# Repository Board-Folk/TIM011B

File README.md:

# TIM-011B

An updated remake of the TIM-011 computer from Serbia.

This repository contains the Bill-of-Materials (BOM), Gerbers and Kicad files for a remake of the TIM-011 from the Mihajlo Pupin Institute of Serbia, 1987.

The TIM-011 is a CP/M based computer that uses the Z80 family Hitachi HD64180 processor with 256KB RAM, 4 scale monochrome video and a FDC9266 floppy disk controller on the main board. It has an expansion bus, serial and parallel port and an ASCII keyboard interface. The system is built entirely from off-the-shelf parts that were commonly available at the time without any custom ULA or gate array chips. Most parts remain relatively easy to get hold of today online.

Version 1.1 does not deviate from the original board too much so it can still be considered a replica.

Version 1.2 includes 5V only operation, but due to stability issues this has not been published.

Version 1.3 contains improvements including composite video output, updated oscillators and stability fixes and uses a GAL for video sync signals. The initial version of this GAL is incompatible with the original screen, a modified version may be added in the future. From version 1.3, the board changed from using HC-49 crystals to TTL output DIP8 layout "square" can type oscillators.

Feel free to fork and make your own mods outside of this repository. Folder Extensions contains add on expansions and adapters for the board. More will follow over time.

The work-in-progress version of the board has been removed from this project. If you're looking to make one, pick the latest version from the Releases folder.

Projects are in Kicad 8.

## Building the board

A BOM is present in each release folder. The Kicad iBOM plugin has also been used to create an interactive BOM in the BOM subfolders for the main boards and expansion boards. Since these builds use obsolete parts, such as the CPU, FDC and RAM, we cannot provide any links to those parts. They are available on AliExpress and eBay, but many sellers will ship relabeled or faulty ICs. Be careful.

## Using the board

### Power

Version 1.1, as the original board requires 5V, 12V and -12V power. Power connectors on the board are the original Ei Niš connector P2, but due to the lack of availability of this part we've added P5, a standard 4 pin 3.96mm pin header to the rear of the board. 

Version 1.3 has a centre positive DC barrel jack for only 5V operation also.

### Video

Original video output is not standard, conversion is needed for use on a modern display. This works directly with the original screen and is the only output option on boards until version v1.3. The video fix extension board gives conversion to composite video for boards up to release v1.1. As a technical note, the original video output is provided as 2 TTL signals to giving 4 shades, with a relatively wide horizonal and vertical sync for the original CRT. The horizontal sync is in an awkward position and is more simlar to horizonal drive found on comparible systems with a simple in-build CRT display.

Version 1.3 adds a composite video output for use on standard monitors.

### Keyboard

The keyboard is serial ASCII, 9600 8E1 with a 12V power output on the 5 pin DIN header. Version 1.3 adds the option to switch this to 5V operation. Adapter boards are being added to the extensions folder for this and will also including modules for the v1.3 mainboard to contain keyboard conversion within the board footprint.

No operating system is included within the ROM - it needs to boot this from floppy disk or equivalent Gotek or Flash Floppy device. Marko's updated ROM for v1.3, which is backwards compatable adds diagnotics and support to boot from CF cards with the 8 bit CF/IDE expansion board and adapter.

More information to follow.

## TIM011 Resources

Marko Šolajić has put a great page together with a ROM, boot disks, software and other resources to help get the TIM-011 going. Highly recommended. The standard "sys", system ROM is 8KB, this will fit on the currently still manufactured and widely available AT28C64B.

  [TIM011 Resources](https://blog.8bitchip.info/tim011-resources/)
  
Marko is also documenting system software and has provided a new boot ROM. These can be found here:

  [TIM011 System Software](https://github.com/msolajic/tim011-system-software)

## Revisions

* Version 1.1 Initial Public Release
* Version 1.2 Unreleased
* Version 1.3 Current Release
  
### Version 1 Modifications from Original

* Fixed VSYNC Buffer
* Fix Strobe Pullup
* CX timing fix capacitor
* P5 3.96mm right angle power pin header 
* XT Keyboard INT0/SCROLL fix modification with JMP3 selection on/off
* Right angle reset momentatary switch within T1 footprint
* Modernise J3 keyboard connector footprint
* J4 and J5 serial pin headers for alternative serial connections
* Added mounting holes
* Power LED

### Version 1.1

* C42 silkscreen
* Fix J4 and J5 connections
* Silkscreen updates
* ROM A13 to GND
* Increase DB25 mounting point radius to 1.6mm
* Add JMP4 drive Ready/Disk Change modification

### Version 1.2

* 5V Only operation - added DC barrel jack
* Ceramic caps changed to 5.08mm
* Updated silkscreen
* JMP5 5V/12V keyboard selection
* A13,A14,A15 ROM options
* JMP8 No Video jumper
* Change serial to MAX232 (5V)
* RAM change to 44256
* "Half-can" Oscillators for X1 and X2
* JMP9 12V Power selection for expansion bus pin 40
* Grounding point
* Support for keyboard modules

### Version 1.3

* Replaced U2 74LS08 with GAL16V8
* Sync signals negative with standard GAL
* Change serial port to 9 pin
* Oscillators now buffered
* R8 reset pullup
* Composite video output

## Version 1.3 BOM

There are 3 options for board power, P2, P5 or P7. Ceramic capacitors 5.08mm and resistors 1/4W.

|Qty|Reference(s)|Value|Type|Notes|
|:--:|:--:|:--:|:--:|:--:|
|1|P1|5-7 pin header|Header|Video|
|1|P3|2x20 pin header|Dual Row 2.54mm Header|Expansion|
|1|P4|2x17 pin header|Dual Row 2.54mm Header|Floppy|
|1|P2|Unknown Ei Niš 4 pin header|Header|Power|
|1|P5|3.96mm 4 pin header|3.96mm Header|Alt Power|
|1|P7|DC Barrel Jack||5V Power|
|1|P8|RCA Jack||Composite Output|
|46|C3, C8, C10-C53|100nF|Ceramic Capacitor||
|1|C2|1nF|Ceramic Capacitor||
|1|C4|10uF 16V|Axial or Radial||
|1|C5|2n2|Ceramic Capacitor||
|1|C6|470uF 25V|Axial or Radial||
|8|C54-C57, C58-C61|1uF 16V|Radial||
|1|CX1, CX2|330pF|Ceramic Capacitor||
|1|D1|1N4148|Diode||
|1|D1|3mm LED|LED||
|2|R1, R12|470R|Resistor||
|1|R10|1K5|Resistor||
|1|R11|5K1|Resistor||
|2|R13, R20|1K|Resistor||
|1|R14|220R|Resistor||
|1|R15|10K|Resistor||
|1|R16|68R|Resistor||
|5|R2-R5, R7|4K7|Resistor||
|1|R6|100R|Resistor||
|1|R8|56K|Resistor||
|1|R9|2K2|Resistor||
|2|RP1, RP2|4K7 SIP10 Bussed|Resistor Network||
|1|RP3|330R SIP10 Bussed|Resistor Network||
|1|Q1|BC557|Transistor||
|1|U17|HD64180|IC|CPU|
|1|U43|FDC9266|IC|Floppy Controller|
|2|U8, U9|MAX232|IC|Serial Line Driver/Receiver|
|1|U16|27xxx ROM|IC|System ROM|
|2|U60, U61|44256 DRAM|IC|System RAM|
|1|U30|43256 SRAM|IC|Video RAM|
|1|U2|GAL16V8|IC|Sync Logic|
|1|U1|74LS08|IC||
|2|U11, U12|74LS283|IC||
|2|U14, U44|74LS240|IC||
|1|U18|74LS20|IC||
|7|U19-U22, U26-U28|74LS157|IC||
|1|U23|74LS00|IC||
|1|U24|74LS04|IC||
|1|U29|74HC153|IC||
|2|U3, U13|74HC4040|IC||
|1|U31|74LS32|IC||
|1|U32|74LS139|IC||
|1|U33|74LS07|IC||
|1|U34|74LS06|IC||
|1|U35|74LS158|IC||
|5|U4-U6, U40, U41|74LS374|IC||
|1|U42|74LS244|IC||
|4|U7, U10, U15, U25|74LS74|IC||
|1|T1|Unknown Reset Switch|Switch|T1 or T2|
|1|T2|RA Momentary Switch|Switch||
|1|J1|DB25 Female Right Angle|Socket|Printer|
|1|J3|5 pin DIN|Socket|180 degree / ASCII Keyboard|
|2|J4, J5|4 pin header|2.54mm Header|Alt TTL Serial|
|1|J6|DB9 Male Right Angle|Socket|Serial|
|1|JMP1, JMP3, JMP5-8|3 pin header|2.54mm Header||
|1|JMP2|5 pin header|2.54mm Header||
|1|JMP4|2 pin header|2.54mm Header|Fix Ready/Disk Change|
|1|X1|12.288MHz TTL Osc Can (DIP8)|Oscillator||
|1|X2|8MHz TTL Osc Can (DIP8)|Oscillator||

## Jumper Settings

Version 1.3

|Jumper|Description|Default|
|:--:|:--:|:--:|
|JMP1|CTS0 Select|2-3|
|JMP2|CTS/DCD Select|4-5,7-8|
|JMP3|XT Keyboard Fix|1-2 D Normal, 2-3 U Fix|
|JMP4|FDC Ready|Optional|
|JMP5|Keyboard Power|1-2 D 12V, 2-3 U 5V|
|JMP6|ROM A14|1-2 L 5V, 2-3 R A14|
|JMP7|ROM A15|1-2 L 5V, 2-3 R A15|
|JMP8|Video Bypass|1-2 U Normal, 2-3 D Disable|
|JMP9|12V Expansion Pin 40|NF|
|JMP10|HSYNC connection for CSYNC|Preset ON|

## Links

   [Marko's Blog Post on the TIM 011](https://blog.8bitchip.info/482-tim-011-a-new-life-for-an-old-computer/)

## Credits

PCB Layout by Rob Taylor @peepouk, Ian Cudlip @grandoldian and Marko Šolajić @msolajic. Schematics recreated and modifications by Ian Cudlip and Marko Šolajić. Special thanks to @demerzel, your schematics have helped and saved time.

## Thanks

* Zoltan Pekic
* @demerzel
* The Board Folk Team

## Legal

As the product of this project is a replica of a proprietary product, the the author makes no claim of copyright to the schematics nor PCB layouts and releases these into the public domain, solely for the purposes of study and historical preservation.

You are free to produce PCBs based on this project's designs at your own risk and without limitation, for your own use or for sale and/or repair at a reasonable price. Attribution is appreciated. The authors are not obliged to provide support of any kind. 

Under no circumstances will the authors be held responsible or liable in any way for losses, damages or costs resulting from the use of the information and/or resources of this project. 

The resources are provided "as-is" without warranty of any kind, either expressed or implied, including, but not limited to, the implied warranties of merchantability and fitness for a particular purpose.

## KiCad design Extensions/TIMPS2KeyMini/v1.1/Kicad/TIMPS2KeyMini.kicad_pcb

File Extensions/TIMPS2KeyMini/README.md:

# TIMPS2KeyMini

ATMega328 based PS/2 Keyboard Adapter. A daugherboard that will fit within the mainboard footprint instead of the traditional 5 pin DIN ASCII keyboard socket. This includes the i2c connector for the TIMI2CLEDPanel board which provides the LEDs.

## Versions

v1.1 Initial release

## Main board modifications

This fits instead of the external RS232 functionality of the original keyboard and connector (serial port RS232 remains). On the mainboard, do not fit the MAX232 at J9, the 5 pin DIN socket J3 and the charge caps C58-C61, fitting the 4 pin header J5 instead. Standoffs will needed to be mounted to secure the mini keyboard board and the pin length of the J5 header should match the standoff length. Recommendations may follow.

## Programming the ATMega328

The board doesn't include a programming header, the ATMega328 chip needs programming separately. The simplest way of doing this is with a Minipro with the appopriate fuse settings set in Xgpro. Tested settings are in the screenshot below and the exported binary and hex files for programming can be found in the export folder. For the arduino code see the main TIMPS2Key extension folder.

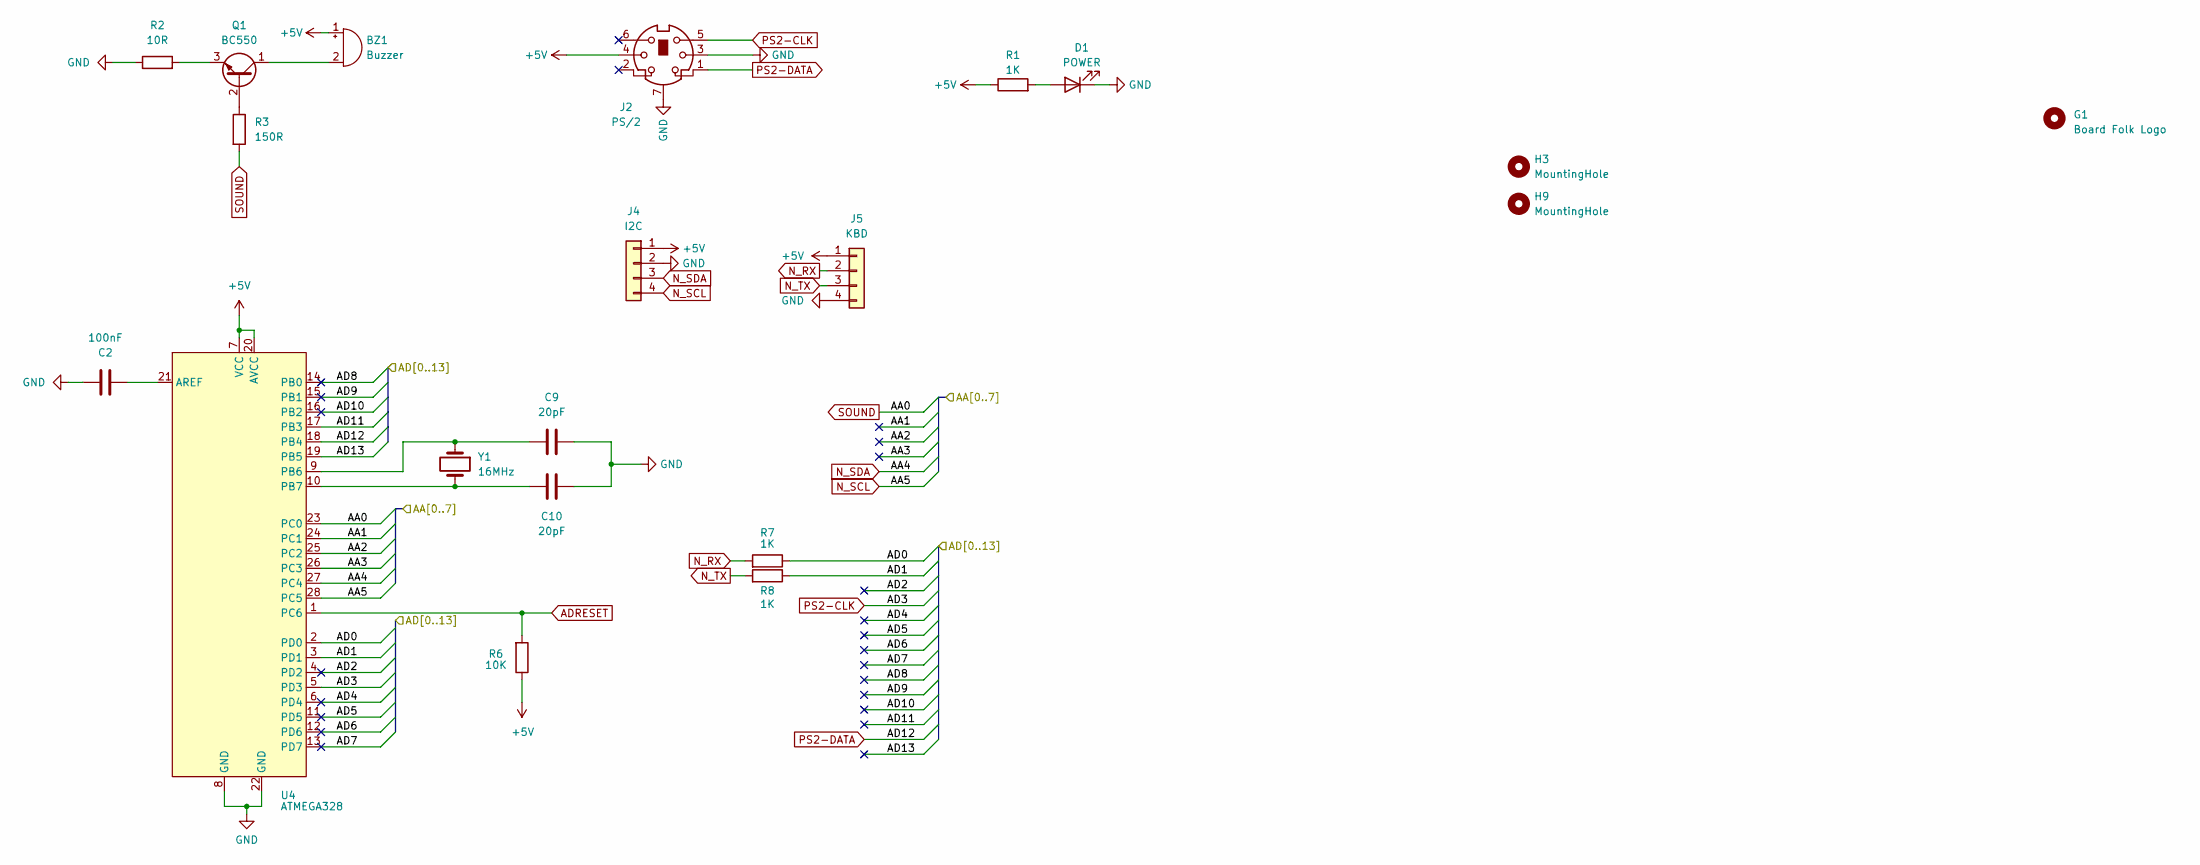
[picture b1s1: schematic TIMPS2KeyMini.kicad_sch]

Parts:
BZ1: Buzzer
C2: 100nF; Ceramic Cap 5.08mm
C9, C10: 20pF; Ceramic Cap 5.08mm
D1: POWER; LED_D3.0mm
G1: Board Folk Logo; BF8
H3, H9: MountingHole; MountingHole_M2.5
J2: PS/2; Connector_Mini-DIN_Female_6Pin_2rows
J4: I2C; PinHeader_1x04_2.54mm
J5: KBD; PinHeader_1x04_2.54mm
Q1: BC550; TO-92_Inline_Wide
R1, R7, R8: 1K; Resistor 7.62mm
R2: 10R; Resistor 7.62mm
R3: 150R; Resistor 7.62mm
R6: 10K; Resistor 7.62mm
U4: ATMEGA328; DIP-28_W7.62mm_Socket
Y1: 16MHz; Crystal_HC49-U_Vertical

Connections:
+5V: BZ1.1 (+), J2.4, J4.1, J5.1, R1.1, R6.1, U4.7 (VCC), U4.20 (AVCC)
/AA1: U4.24 (PC1)
/AA2: U4.25 (PC2)
/AA3: U4.26 (PC3)
/AD0: R7.1, U4.2 (PD0)
/AD1: R8.1, U4.3 (PD1)
/AD2: U4.4 (PD2)
/AD4: U4.6 (PD4)
/AD5: U4.11 (PD5)
/AD6: U4.12 (PD6)
/AD7: U4.13 (PD7)
/AD8: U4.14 (PB0)
/AD9: U4.15 (PB1)
/AD10: U4.16 (PB2)
/AD11: U4.17 (PB3)
/AD13: U4.19 (PB5)
ADRESET: R6.2, U4.1 (PC6)
GND: C2.2, C9.2, C10.2, D1.1 (K), J2.3, J2.7, J4.2, J5.4, R2.1, U4.8 (GND), U4.22 (GND)
N_RX: J5.2, R7.2
N_SCL: J4.4, U4.28 (PC5)
N_SDA: J4.3, U4.27 (PC4)
N_TX: J5.3, R8.2
unnamed: BZ1.2 (-), Q1.1 (C)
unnamed: D1.2 (A), R1.2
unnamed: Q1.2 (B), R3.1
unnamed: Q1.3 (E), R2.2
unnamed: C2.1, U4.21 (AREF)
unnamed: C9.1, U4.9 (PB6), Y1.1
unnamed: C10.1, U4.10 (PB7), Y1.2
PS2-CLK: J2.5, U4.5 (PD3)
PS2-DATA: J2.1, U4.18 (PB4)
SOUND: R3.2, U4.23 (PC0)

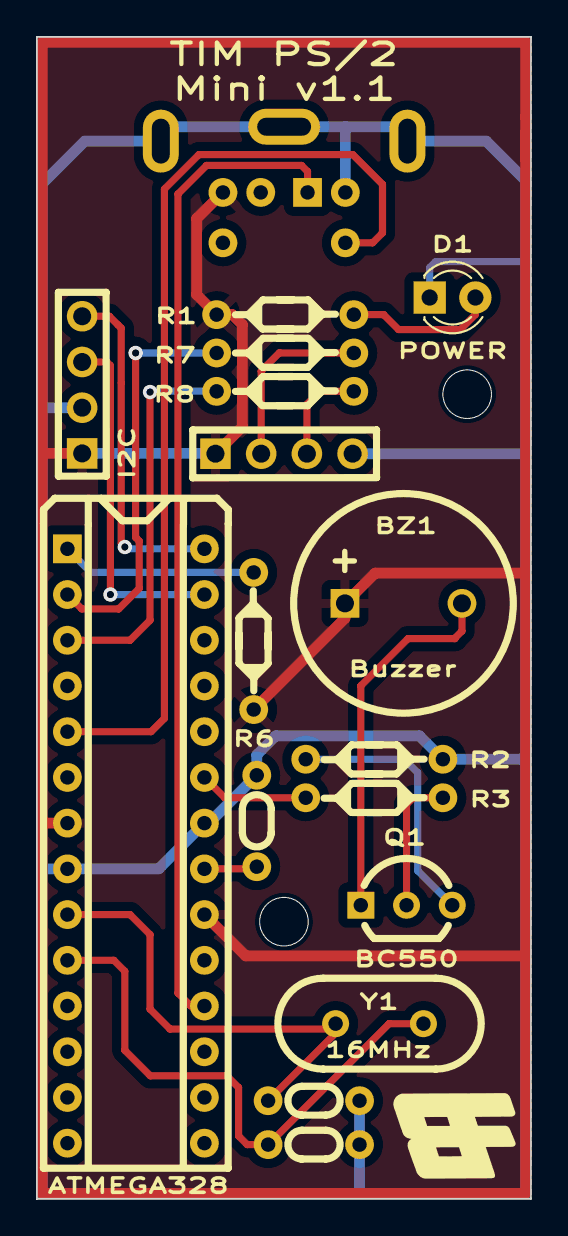
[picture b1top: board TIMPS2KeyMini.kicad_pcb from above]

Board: 2 copper layers, 27.5 x 64.6 mm, 20 parts (1 on the bottom side), 19 nets.

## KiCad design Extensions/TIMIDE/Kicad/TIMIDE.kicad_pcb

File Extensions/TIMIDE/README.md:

# TIMIDE

An 8-bit IDE and Compact Flash interface for the TIM-011 for the expansion header. This requires the updated ROM by Marko Šolajić which can be found here:

  [TIM011 System Software](https://github.com/msolajic/tim011-system-software)

The default IO address for the board as used by the ROM, selectable by jumper is E8. To date we've not found an 8 bit compatable IDE hard disk to work with this board, but a standard Amazon / AliExpress CompactFlash to IDE adapter works fine (pictured).

Marko's site also provides a CF image to get things going.

## Versions

v1 Initial release

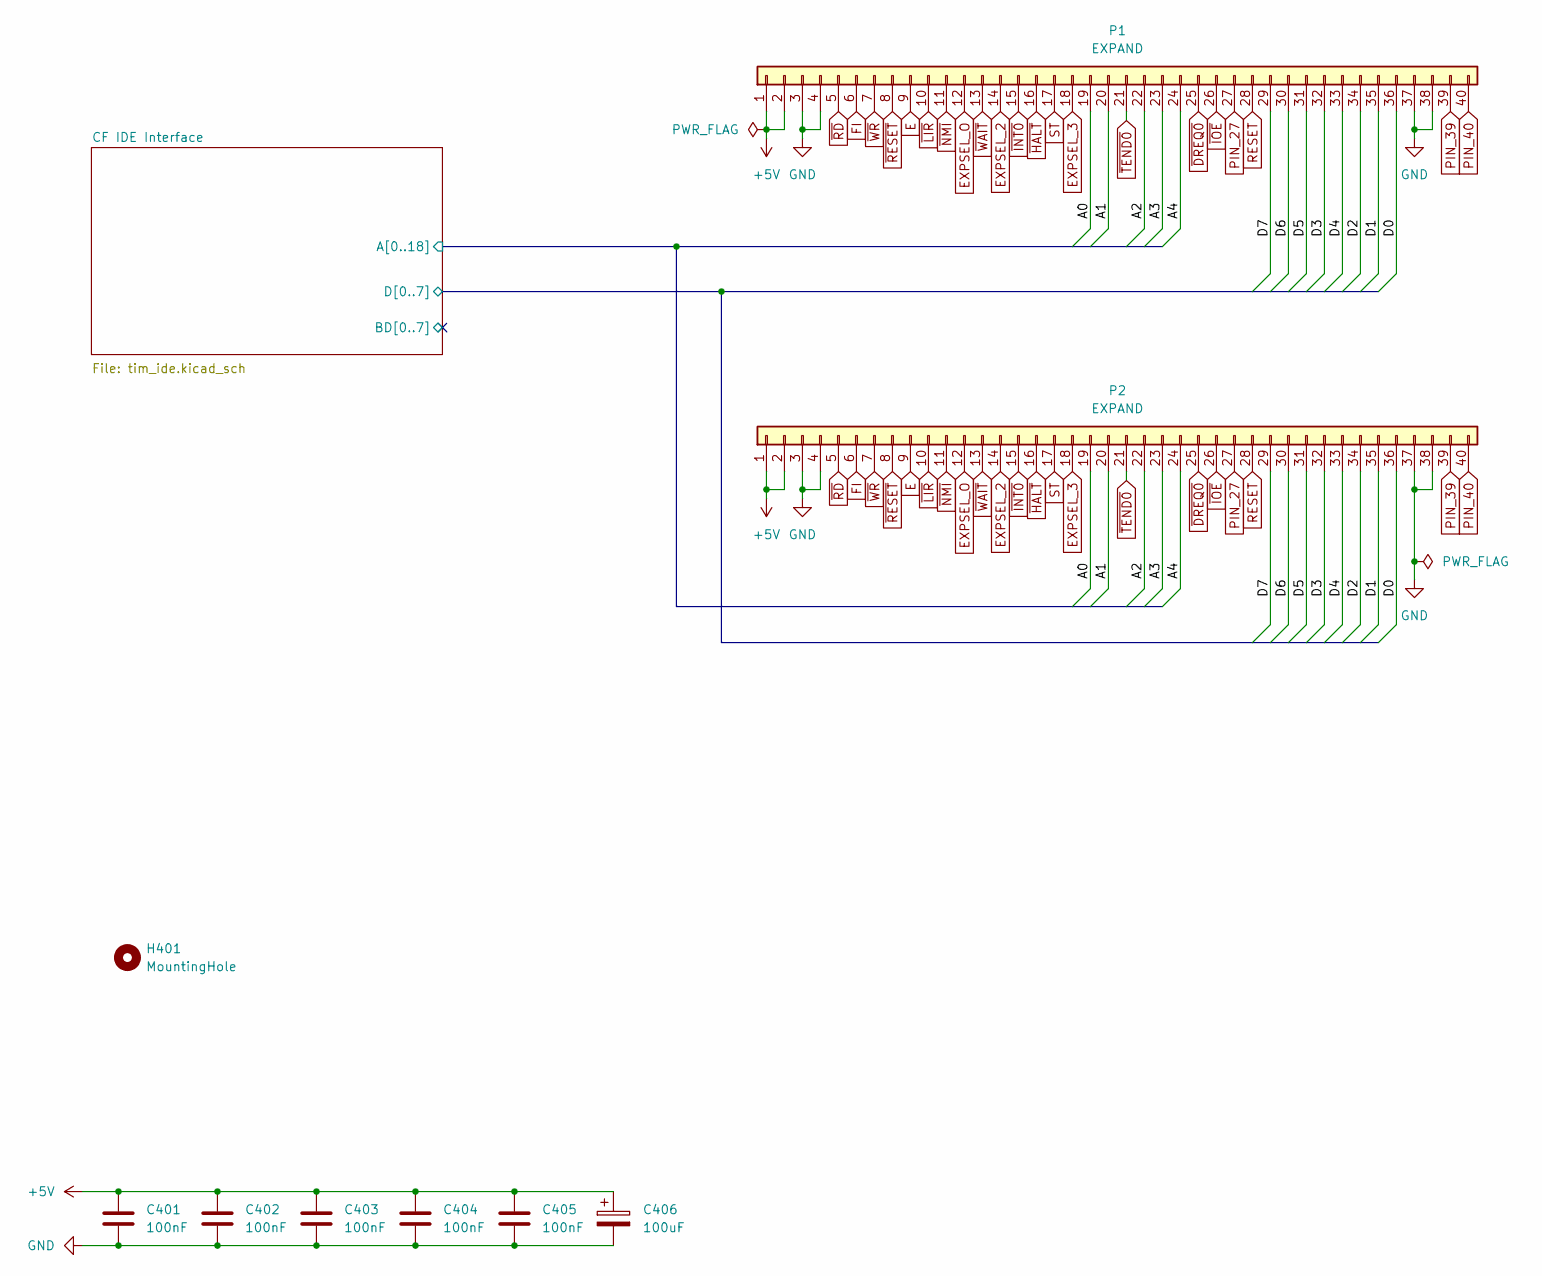
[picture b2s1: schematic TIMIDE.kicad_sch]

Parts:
C401, C402, C403, C404, C405: 100nF; Ceramic Cap 5.00mm
C406: 100uF; Electrolytic Capacitor Axial or Radial Alt
H401: MountingHole; MountingHole_M2.5
P1, P2: EXPAND; PinHeader_2x20 2.54mm

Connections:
+5V: C401.1, C402.1, C403.1, C404.1, C405.1, C406.1, P1.1, P1.2, P2.1, P2.2; also elsewhere on the board
/CF IDE Interface/A0: P1.19, P2.19; also elsewhere on the board
/CF IDE Interface/A1: P1.20, P2.20; also elsewhere on the board
/CF IDE Interface/A2: P1.22, P2.22; also elsewhere on the board
/CF IDE Interface/A3: P1.23, P2.23; also elsewhere on the board
/CF IDE Interface/A4: P1.24, P2.24; also elsewhere on the board
/CF IDE Interface/D0: P1.36, P2.36; also elsewhere on the board
/CF IDE Interface/D1: P1.35, P2.35; also elsewhere on the board
/CF IDE Interface/D2: P1.34, P2.34; also elsewhere on the board
/CF IDE Interface/D3: P1.32, P2.32; also elsewhere on the board
/CF IDE Interface/D4: P1.33, P2.33; also elsewhere on the board
/CF IDE Interface/D5: P1.31, P2.31; also elsewhere on the board
/CF IDE Interface/D6: P1.30, P2.30; also elsewhere on the board
/CF IDE Interface/D7: P1.29, P2.29; also elsewhere on the board
E: P1.9, P2.9
EXPSEL_2: P1.14, P2.14
EXPSEL_3: P1.18, P2.18
EXPSEL_O: P1.12, P2.12; also elsewhere on the board
FI: P1.6, P2.6; also elsewhere on the board
GND: C401.2, C402.2, C403.2, C404.2, C405.2, C406.2, P1.3, P1.4, P1.37, P1.38, P2.3, P2.4, P2.37, P2.38; also elsewhere on the board
PIN_27: P1.27, P2.27
PIN_39: P1.39, P2.39
PIN_40: P1.40, P2.40
RESET: P1.28, P2.28
ST: P1.17, P2.17
~DREQ0: P1.25, P2.25
~HALT: P1.16, P2.16
~INT0: P1.15, P2.15
~IOE: P1.26, P2.26
~LIR: P1.10, P2.10; also elsewhere on the board
~NMI: P1.11, P2.11
~RD: P1.5, P2.5; also elsewhere on the board
~RESET: P1.8, P2.8; also elsewhere on the board
~TEND0: P1.21, P2.21
~WAIT: P1.13, P2.13
~WR: P1.7, P2.7; also elsewhere on the board

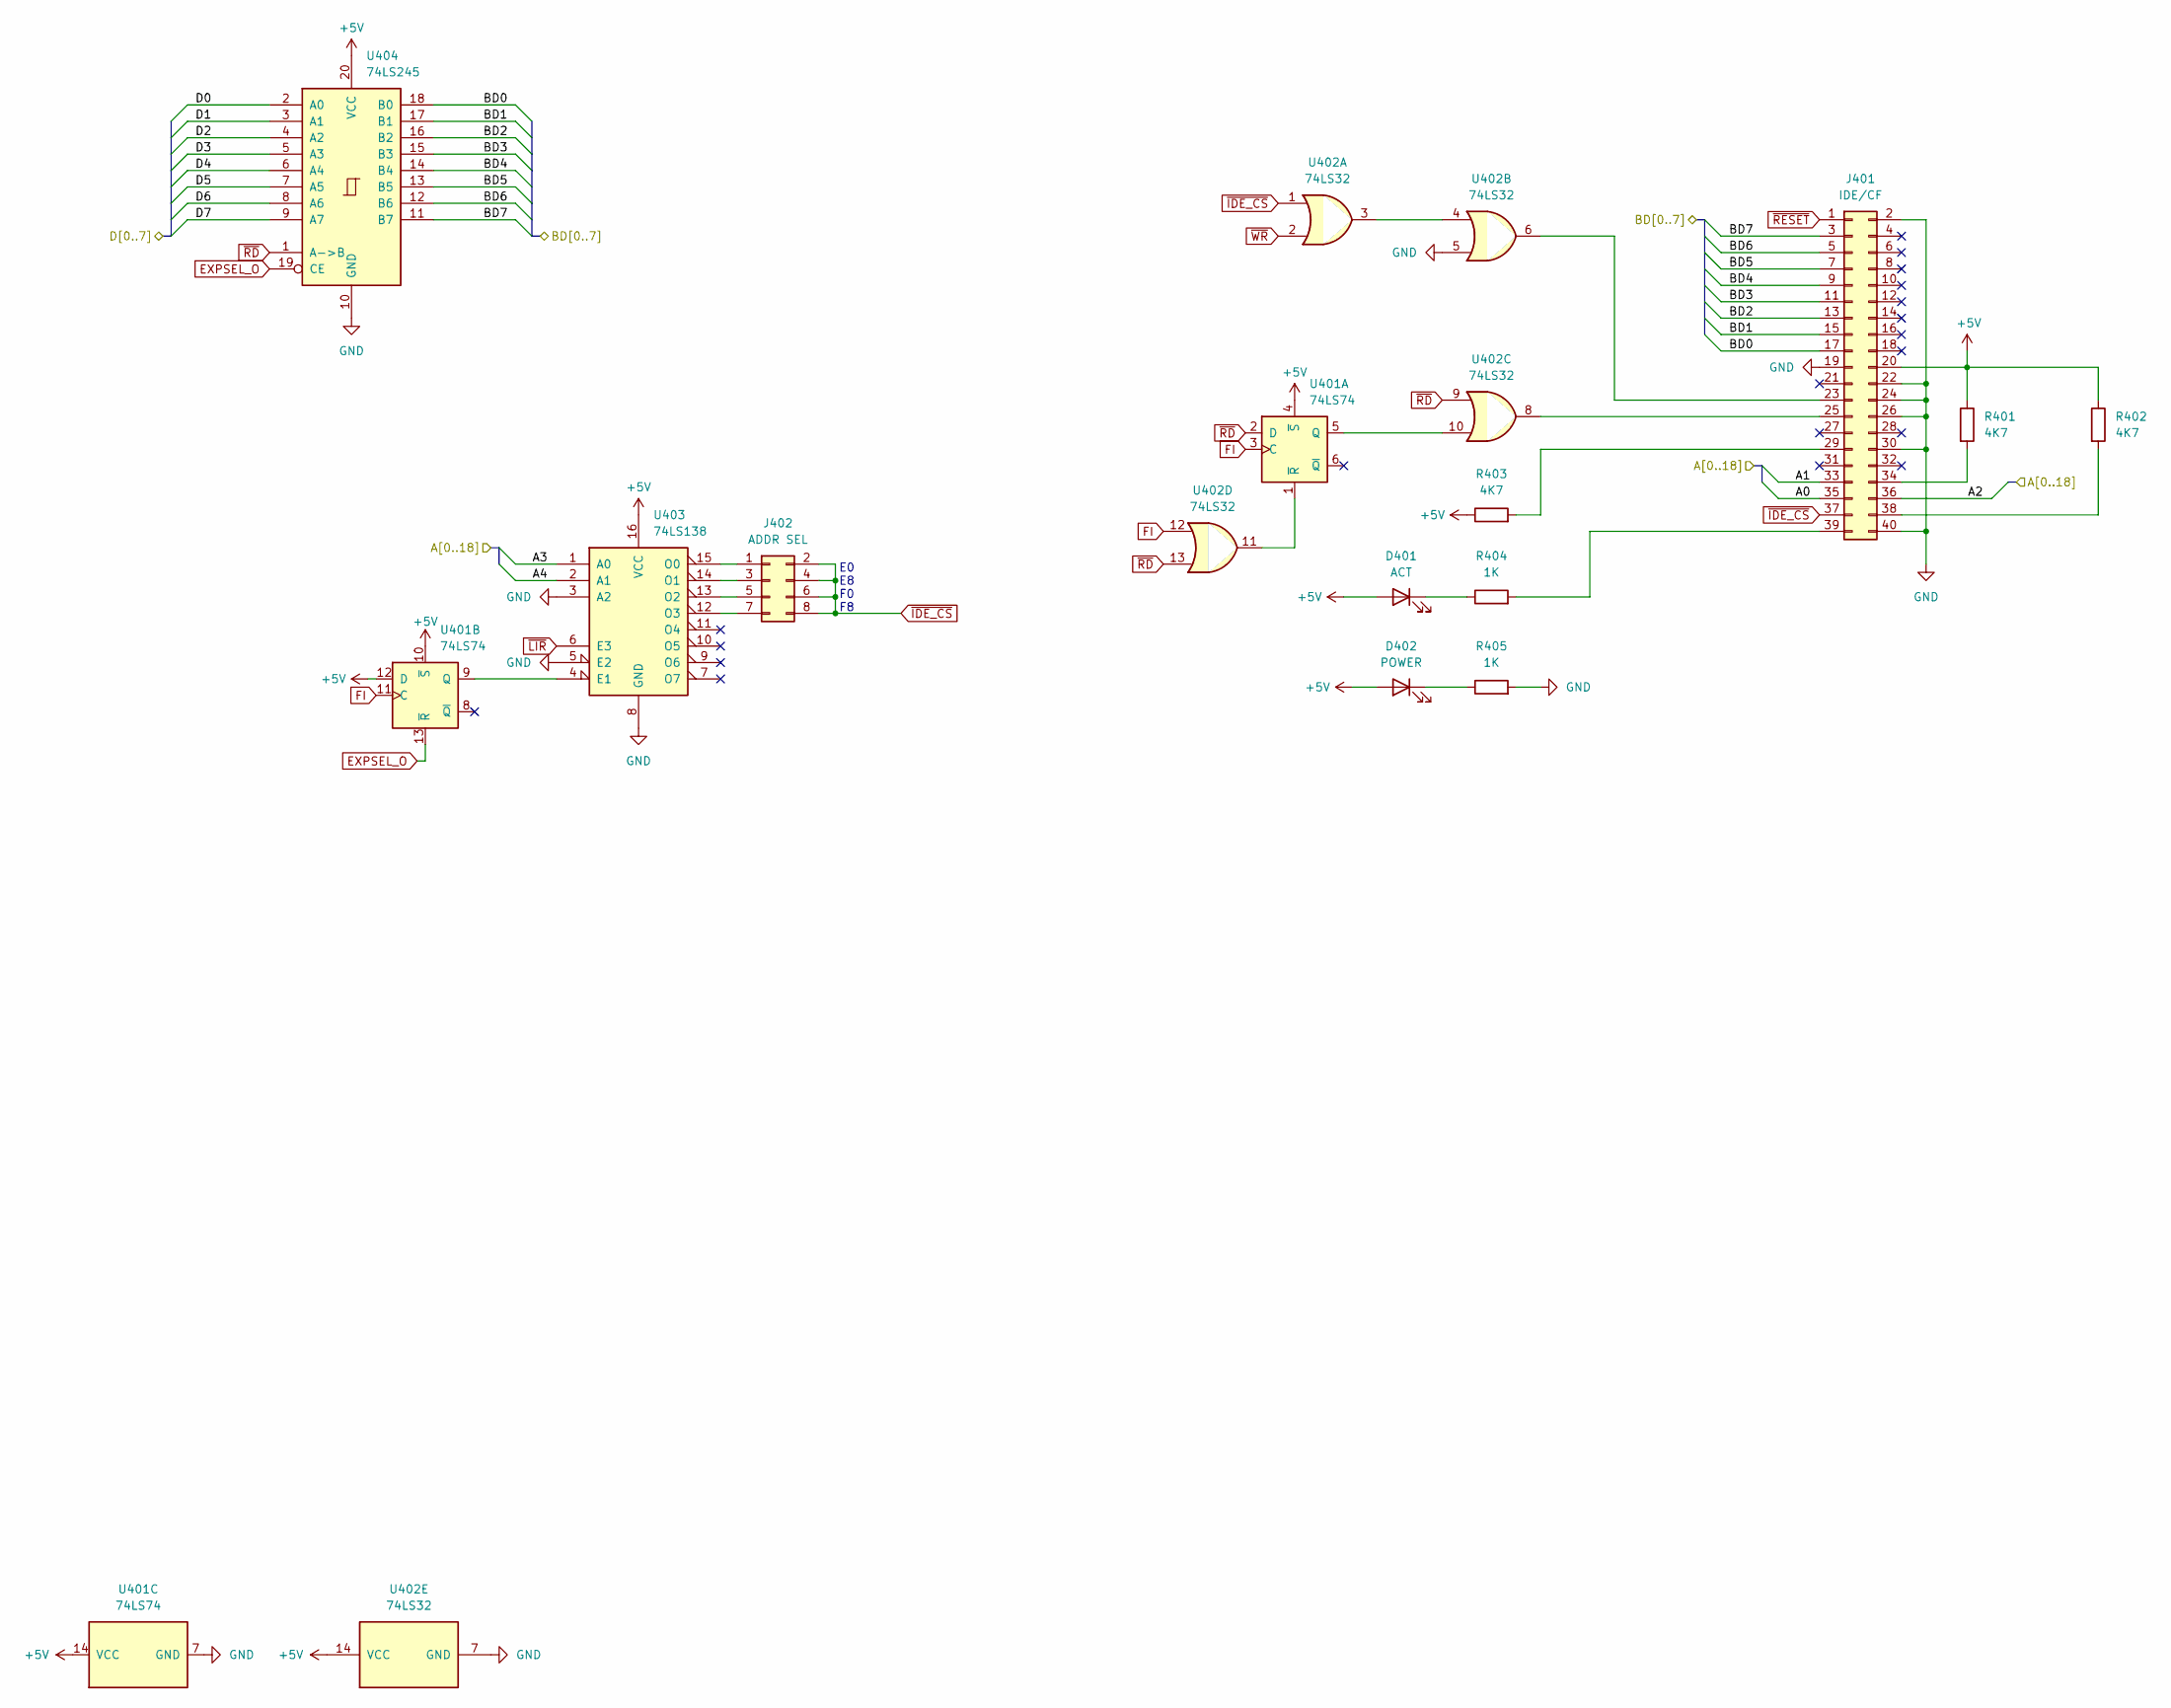
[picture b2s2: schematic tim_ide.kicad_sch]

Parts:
D401: ACT; TIM_LED_D3.0mm
D402: POWER; TIM_LED_D3.0mm
J401: IDE/CF; PinHeader_2x20 2.54mm
J402: ADDR SEL; TIM_Address_2x04
R401, R402, R403: 4K7; Resistor 12.7mm
R404, R405: 1K; Resistor 12.7mm
U401: 74LS74; DIP-14_W7.62mm
U402: 74LS32; DIP-14_W7.62mm
U403: 74LS138; DIP-16_W7.62mm
U404: 74LS245; DIP-20_W7.62mm

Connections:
+5V: D401.2 (A), D402.2 (A), J401.20, R401.1, R402.1, R403.1, U401.4 (~S), U401.10 (~S), U401.12 (D), U401.14 (VCC), U402.14 (VCC), U403.16 (VCC), U404.20 (VCC); also elsewhere on the board
/CF IDE Interface/A0: J401.35; also elsewhere on the board
/CF IDE Interface/A1: J401.33; also elsewhere on the board
/CF IDE Interface/A2: J401.36; also elsewhere on the board
/CF IDE Interface/A3: U403.1 (A0); also elsewhere on the board
/CF IDE Interface/A4: U403.2 (A1); also elsewhere on the board
/CF IDE Interface/BD0: J401.17, U404.18 (B0)
/CF IDE Interface/BD1: J401.15, U404.17 (B1)
/CF IDE Interface/BD2: J401.13, U404.16 (B2)
/CF IDE Interface/BD3: J401.11, U404.15 (B3)
/CF IDE Interface/BD4: J401.9, U404.14 (B4)
/CF IDE Interface/BD5: J401.7, U404.13 (B5)
/CF IDE Interface/BD6: J401.5, U404.12 (B6)
/CF IDE Interface/BD7: J401.3, U404.11 (B7)
/CF IDE Interface/D0: U404.2 (A0); also elsewhere on the board
/CF IDE Interface/D1: U404.3 (A1); also elsewhere on the board
/CF IDE Interface/D2: U404.4 (A2); also elsewhere on the board
/CF IDE Interface/D3: U404.5 (A3); also elsewhere on the board
/CF IDE Interface/D4: U404.6 (A4); also elsewhere on the board
/CF IDE Interface/D5: U404.7 (A5); also elsewhere on the board
/CF IDE Interface/D6: U404.8 (A6); also elsewhere on the board
/CF IDE Interface/D7: U404.9 (A7); also elsewhere on the board
EXPSEL_O: U401.13 (~R), U404.19 (CE); also elsewhere on the board
FI: U401.3 (C), U401.11 (C), U402.12; also elsewhere on the board
GND: J401.2, J401.19, J401.22, J401.24, J401.26, J401.30, J401.40, R405.2, U401.7 (GND), U402.5, U402.7 (GND), U403.3 (A2), U403.5 (E2), U403.8 (GND), U404.10 (GND); also elsewhere on the board
unnamed: D401.1 (K), R404.1
unnamed: D402.1 (K), R405.1
unnamed: J401.23, U402.6
unnamed: J401.25, U402.8
unnamed: J401.29, R403.2
unnamed: J401.34, R401.2
unnamed: J401.38, R402.2
unnamed: J401.39, R404.2
unnamed: J402.1, U403.15 (O0)
unnamed: J402.3, U403.14 (O1)
unnamed: J402.5, U403.13 (O2)
unnamed: J402.7, U403.12 (O3)
unnamed: U401.5 (Q), U402.10
unnamed: U401.1 (~R), U402.11
unnamed: U401.9 (Q), U403.4 (E1)
unnamed: U402.3, U402.4
~IDE_CS: J401.37, J402.2, J402.4, J402.6, J402.8, U402.1
~LIR: U403.6 (E3); also elsewhere on the board
~RD: U401.2 (D), U402.9, U402.13, U404.1 (A->B); also elsewhere on the board
~RESET: J401.1; also elsewhere on the board
~WR: U402.2; also elsewhere on the board

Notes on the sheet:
E0 E8 F0 F8

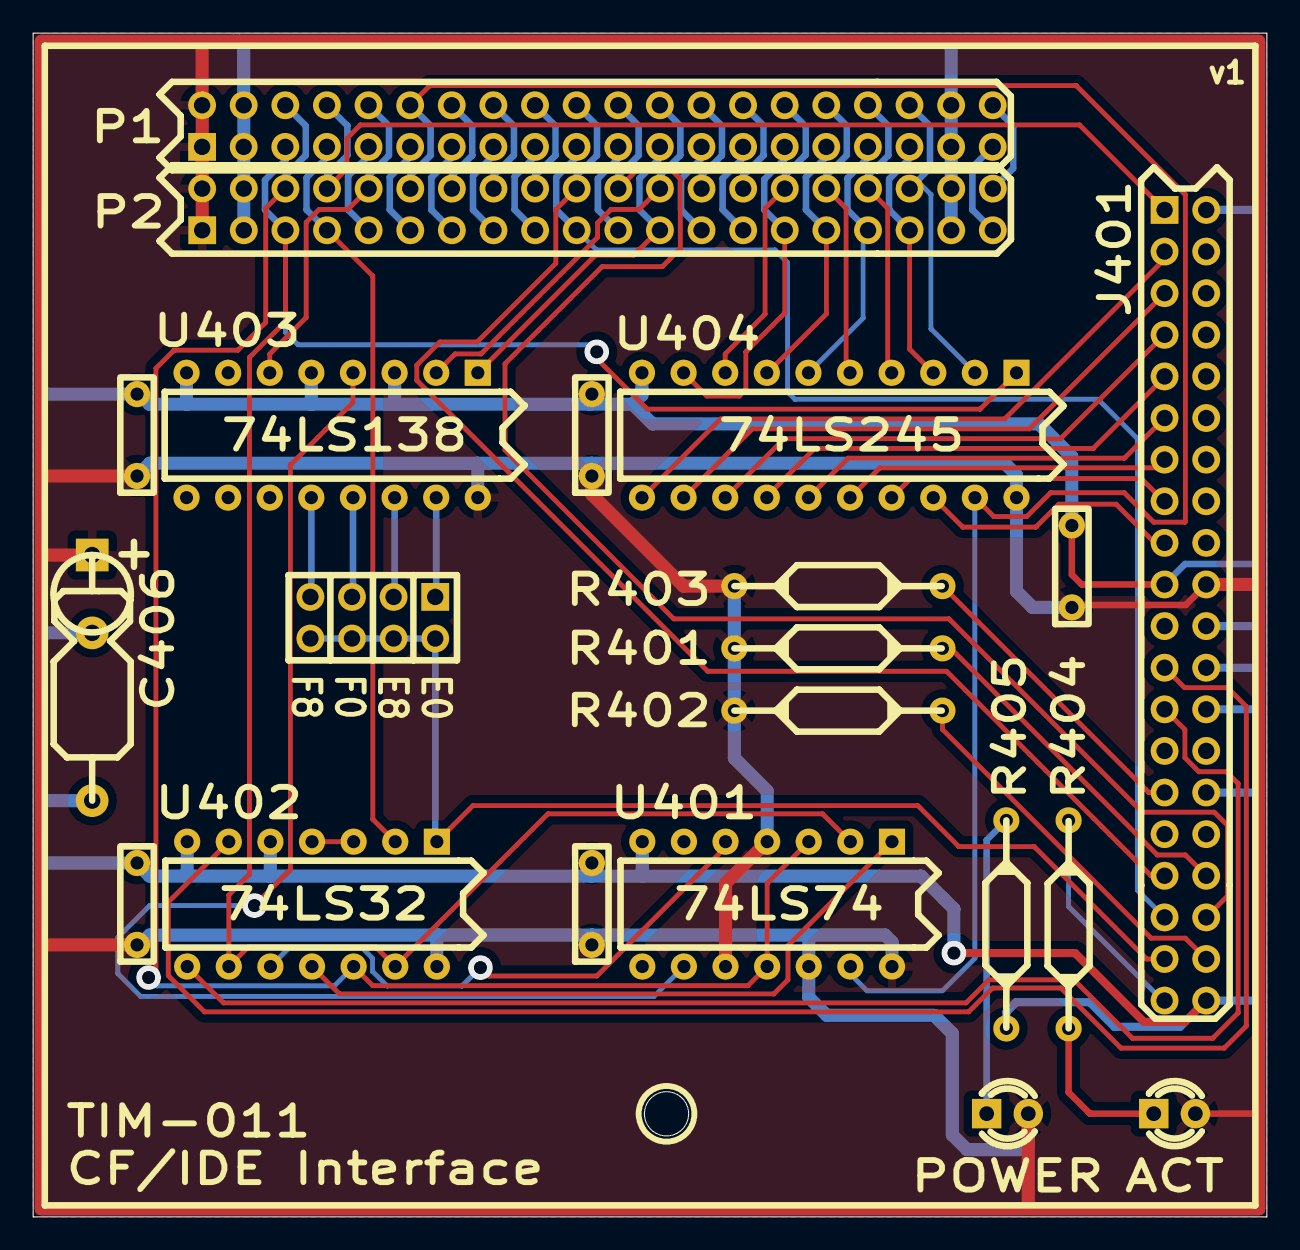
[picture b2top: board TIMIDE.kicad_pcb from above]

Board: 2 copper layers, 75.3 x 72.2 mm, 22 parts (0 on the bottom side), 61 nets.

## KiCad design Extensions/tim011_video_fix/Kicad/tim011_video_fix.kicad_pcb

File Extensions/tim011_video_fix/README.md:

# tim011_video_fix

Video output board to create RGB and composite output from standard TIM-011 video signaling.

Early and original boards need a separate 5V power supply on the pin header provided.

## Versions

v1.1 Initial release

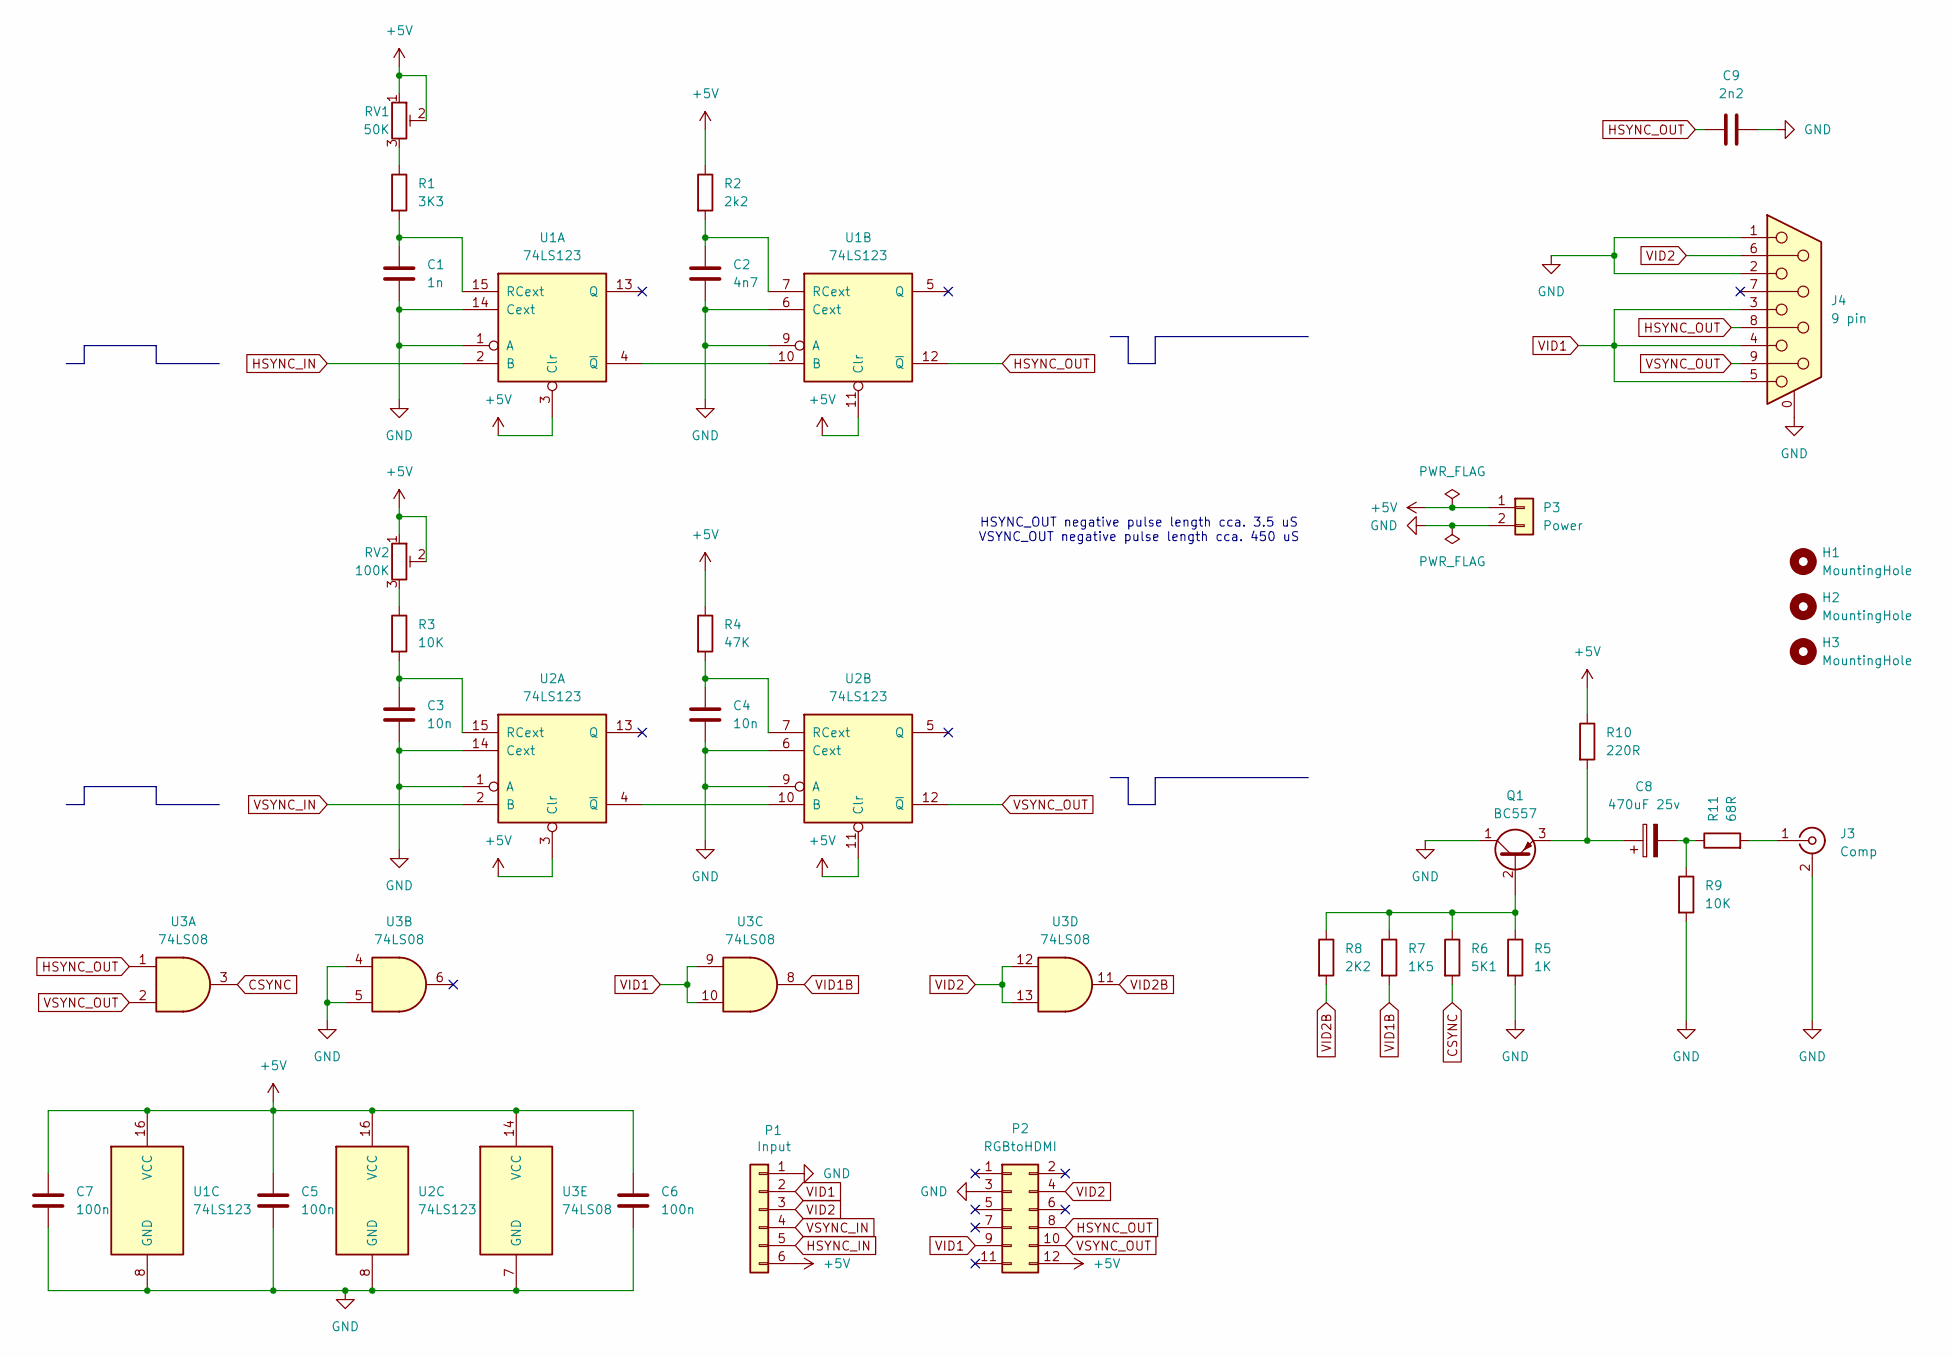
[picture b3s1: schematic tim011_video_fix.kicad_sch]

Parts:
C1: 1n; Ceramic Cap 5.00mm
C2: 4n7; Ceramic Cap 5.00mm
C3, C4: 10n; Ceramic Cap 5.00mm
C5, C6, C7: 100n; Ceramic Cap 5.00mm
C8: 470uF 25v; Electrolytic Capacitor Axial or Radial Alt
C9: 2n2; Ceramic Cap 5.00mm
H1, H2, H3: MountingHole; MountingHole_M2.5
J3: Comp; RCA2
J4: 9 pin; TIM_DSUB-9
P1: Input; PinHeader_1x06 2.54mm
P2: RGBtoHDMI; PinHeader_2x6_2.54mm
P3: Power; 3.96mm Header 2-Pin
Q1: BC557; TO-92_Inline_Wide
R1: 3K3; Resistor 12.7mm
R2: 2k2; Resistor 12.7mm
R3, R9: 10K; Resistor 12.7mm
R4: 47K; Resistor 12.7mm
R5: 1K; Resistor 12.7mm
R6: 5K1; Resistor 12.7mm
R7: 1K5; Resistor 12.7mm
R8: 2K2; Resistor 12.7mm
R10: 220R; Resistor 12.7mm
R11: 68R; Resistor 12.7mm
RV1: 50K; TIM Multi Pot
RV2: 100K; TIM Multi Pot
U1, U2: 74LS123; DIP-16_W7.62mm
U3: 74LS08; DIP-14_W7.62mm

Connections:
+5V: C5.1, C6.1, C7.1, P1.6, P2.12, P3.1, R2.1, R4.1, R10.1, RV1.1, RV1.2, RV2.1, RV2.2, U1.3 (Clr), U1.11 (Clr), U1.16 (VCC), U2.3 (Clr), U2.11 (Clr), U2.16 (VCC), U3.14 (VCC)
CSYNC: R6.2, U3.3
GND: C1.2, C2.2, C3.2, C4.2, C5.2, C6.2, C7.2, C9.2, J3.2 (Ext), J4.0 (PAD), J4.1, J4.2, P1.1, P2.3, P3.2, Q1.1 (C), R5.2, R9.2, U1.1 (A), U1.6 (Cext), U1.8 (GND), U1.9 (A), U1.14 (Cext), U2.1 (A), U2.6 (Cext), U2.8 (GND), U2.9 (A), U2.14 (Cext), U3.4, U3.5, U3.7 (GND)
HSYNC_IN: P1.5, U1.2 (B)
HSYNC_OUT: C9.1, J4.8, P2.8, U1.12 (~Q), U3.1
unnamed: C8.2, R9.1, R11.1
unnamed: J3.1 (In), R11.2
unnamed: Q1.2 (B), R5.1, R6.1, R7.1, R8.1
unnamed: C8.1, Q1.3 (E), R10.2
unnamed: R1.1, RV1.3
unnamed: R3.1, RV2.3
unnamed: C1.1, R1.2, U1.15 (RCext)
unnamed: U1.4 (~Q), U1.10 (B)
unnamed: C2.1, R2.2, U1.7 (RCext)
unnamed: C3.1, R3.2, U2.15 (RCext)
unnamed: U2.4 (~Q), U2.10 (B)
unnamed: C4.1, R4.2, U2.7 (RCext)
VID1: J4.3, J4.4, J4.5, P1.2, P2.9, U3.9, U3.10
VID1B: R7.2, U3.8
VID2: J4.6, P1.3, P2.4, U3.12, U3.13
VID2B: R8.2, U3.11
VSYNC_IN: P1.4, U2.2 (B)
VSYNC_OUT: J4.9, P2.10, U2.12 (~Q), U3.2

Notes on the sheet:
HSYNC_OUT negative pulse length cca. 3.5 uS VSYNC_OUT negative pulse length cca. 450 uS

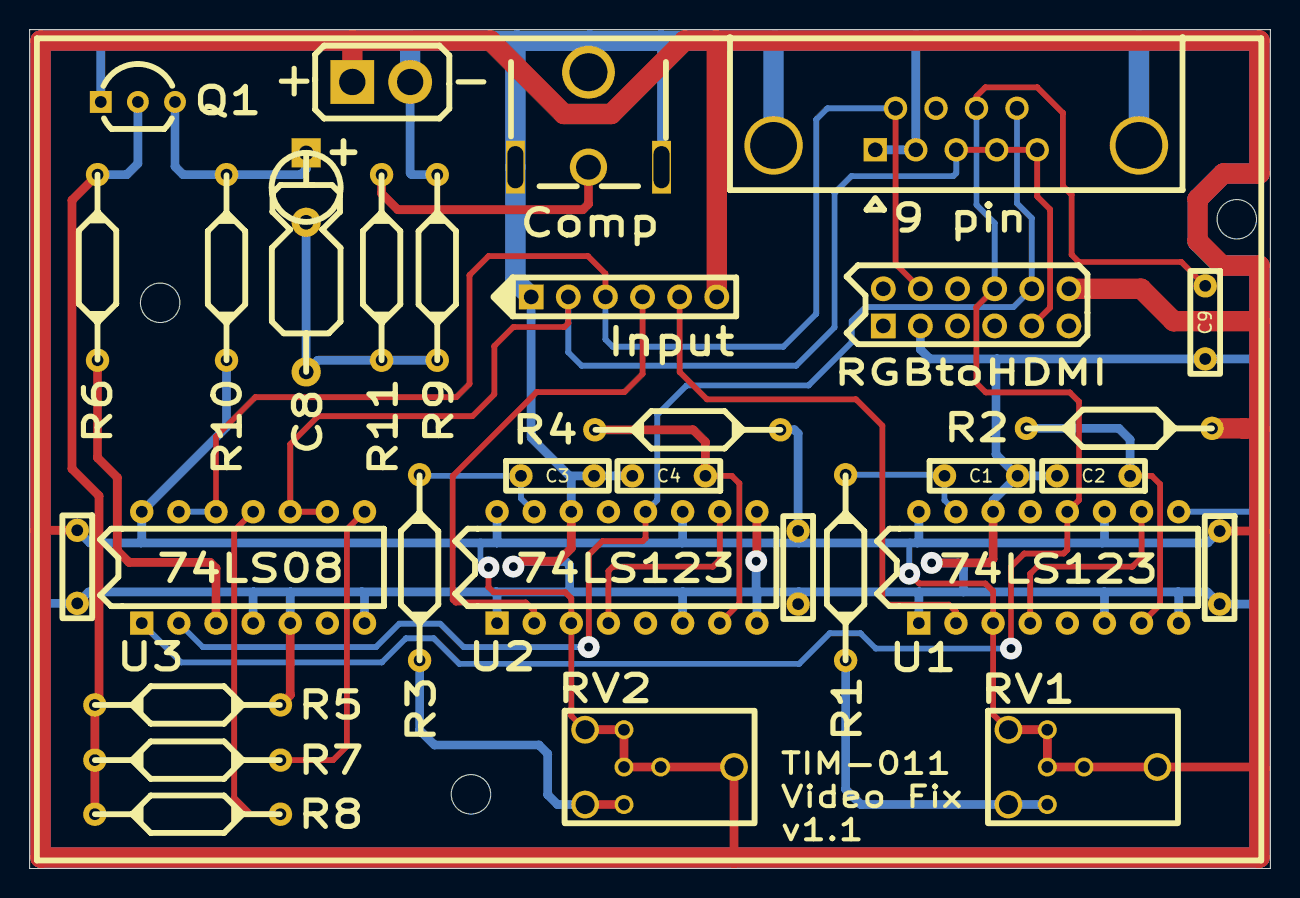
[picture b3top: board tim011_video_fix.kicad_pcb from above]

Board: 2 copper layers, 84.9 x 57.4 mm, 34 parts (0 on the bottom side), 23 nets.
